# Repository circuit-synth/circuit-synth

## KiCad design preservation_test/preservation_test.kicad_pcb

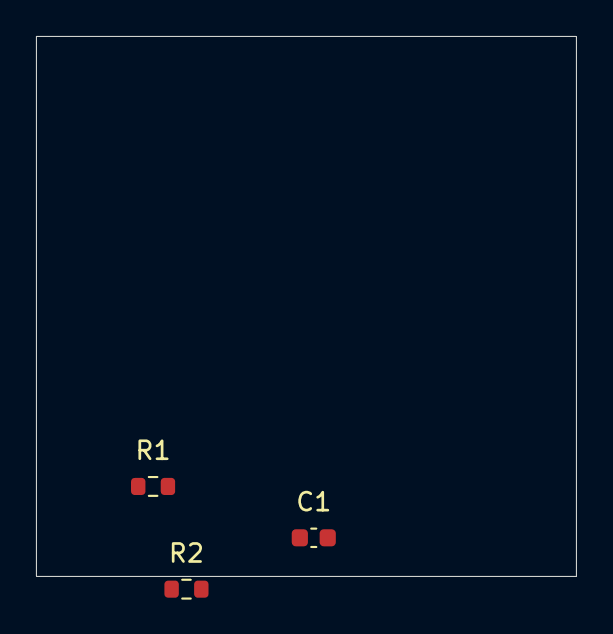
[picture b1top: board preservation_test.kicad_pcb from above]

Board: 2 copper layers, 30.0 x 30.0 mm, 3 parts (0 on the bottom side), 2 nets, no tracks yet.

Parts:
C1: 100nF; C_0603_1608Metric
R1: 10k; R_0603_1608Metric
R2: 1k; R_0603_1608Metric

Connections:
GND: C1.2, R2.2
SIGNAL: C1.1, R1.2, R2.1

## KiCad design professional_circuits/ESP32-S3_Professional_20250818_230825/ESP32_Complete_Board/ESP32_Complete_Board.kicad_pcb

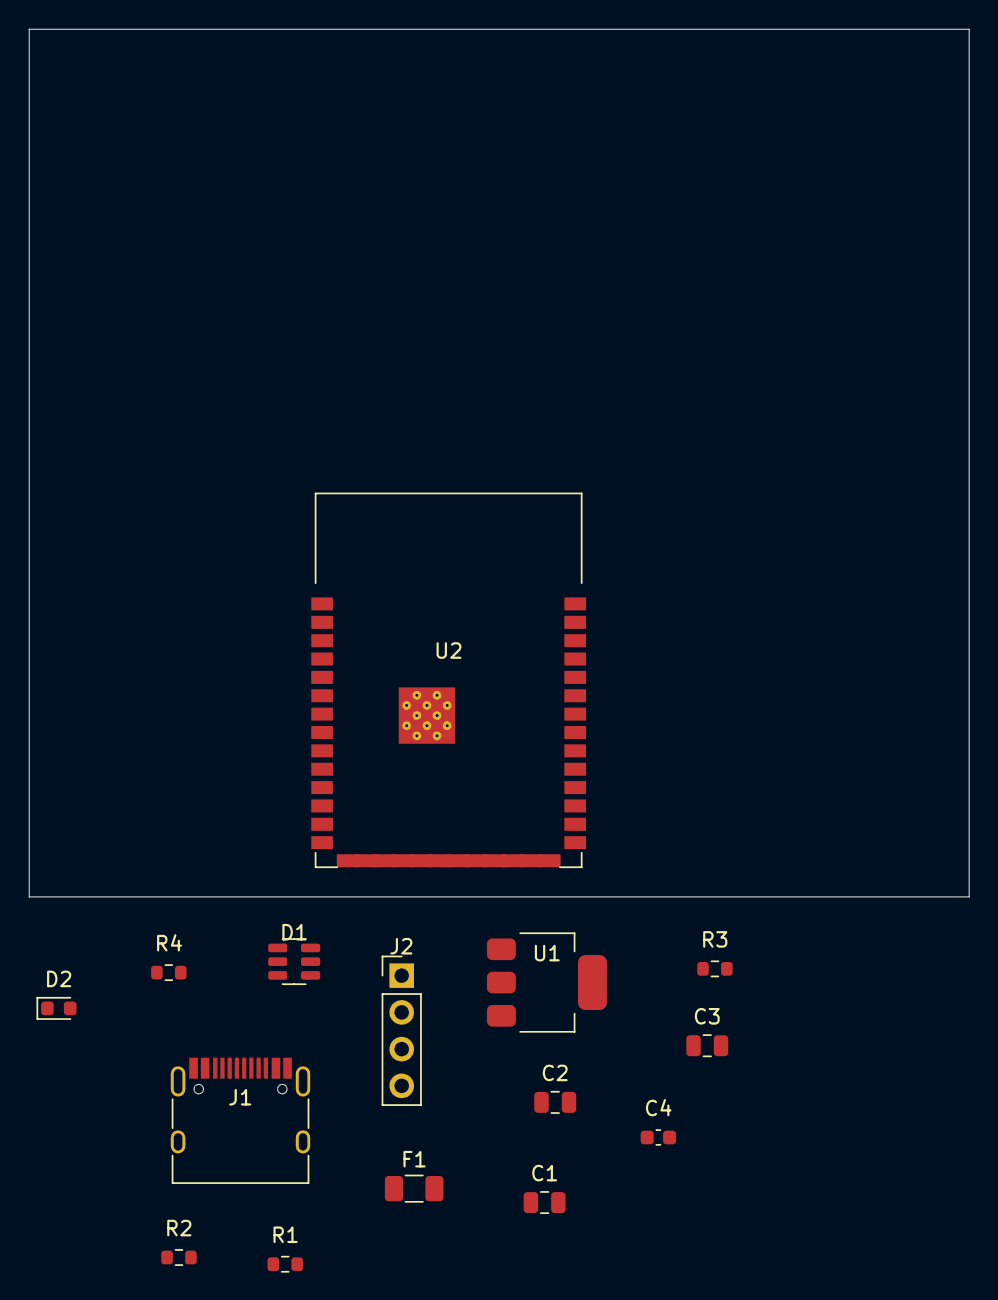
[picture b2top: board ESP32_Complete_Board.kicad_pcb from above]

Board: 2 copper layers, 65.0 x 60.0 mm, 15 parts (0 on the bottom side), 15 nets, no tracks yet.

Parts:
C1, C3: 10uF; C_0805_2012Metric
C2: 22uF; C_0805_2012Metric
C4: 100nF; C_0603_1608Metric
D1: SOT-23-6
D2: LED_0603_1608Metric
F1: 2A; Fuse_1206_3216Metric
J1: USB_C_Receptacle_HRO_TYPE-C-31-M-12
J2: PinHeader_1x04_P2.54mm_Vertical
R1, R2: 5.1k; R_0603_1608Metric
R3: 10k; R_0603_1608Metric
R4: 220; R_0603_1608Metric
U1: SOT-223-3_TabPin2
U2: ESP32-S3-WROOM-1

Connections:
DEBUG_RX: J2.4, U2.36
DEBUG_TX: J2.3, U2.37
GND: C1.2, C2.2, C3.2, C4.2, D1.2, D2.1, J1.A1, J1.A12, J1.B1, J1.B12, J2.2, R1.2, R2.2, U1.1, U2.1, U2.40, U2.41
LED_CONTROL: R4.1, U2.12
unnamed: F1.1, J1.A4, J1.A9, J1.B4, J1.B9
unnamed: D1.1, J1.A6, J1.B6
unnamed: D1.3, J1.A7, J1.B7
unnamed: J1.A5, R1.1
unnamed: J1.B5, R2.1
unnamed: R3.2, U2.3
unnamed: D2.2, R4.2
USB_DM: D1.4, U2.13
USB_DP: D1.6, U2.14
VBUS: C1.1, D1.5, F1.2, U1.3
VCC_3V3: C2.1, C3.1, C4.1, J2.1, R3.1, U1.2, U2.2

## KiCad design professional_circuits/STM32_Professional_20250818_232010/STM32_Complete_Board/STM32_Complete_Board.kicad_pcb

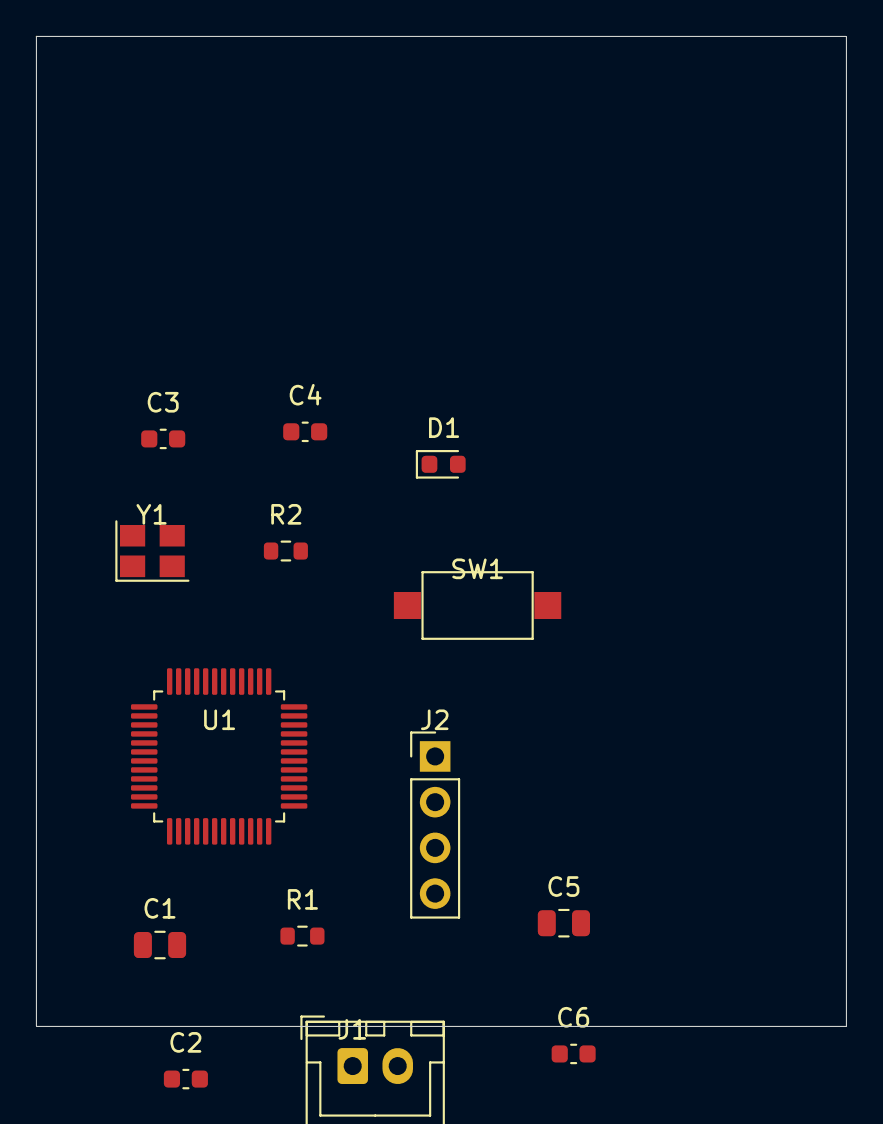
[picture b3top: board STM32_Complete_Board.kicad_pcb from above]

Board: 2 copper layers, 45.0 x 55.0 mm, 14 parts (0 on the bottom side), 9 nets, no tracks yet.

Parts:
C1, C5: 10uF; C_0805_2012Metric
C2, C6: 100nF; C_0603_1608Metric
C3, C4: 18pF; C_0603_1608Metric
D1: LED_0603_1608Metric
J1: JST_XH_B2B-XH-A_1x02_P2.50mm_Vertical
J2: PinHeader_1x04_P2.54mm_Vertical
R1: 10k; R_0603_1608Metric
R2: 220; R_0603_1608Metric
SW1: SW_SPST_CK_RS282G05A3
U1: LQFP-48_7x7mm_P0.5mm
Y1: 8MHz; Crystal_SMD_3225-4Pin_3.2x2.5mm

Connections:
GND: C1.2, C2.2, C3.2, C4.2, C5.2, C6.2, D1.1, J1.2, J2.2, SW1.2, U1.8, U1.23, U1.35, U1.47
LED_CONTROL: R2.1, U1.15
unnamed: C3.1, U1.5, Y1.1
unnamed: C4.1, U1.6, Y1.2
unnamed: D1.2, R2.2
SWCLK: J2.4, U1.37
SWDIO: J2.3, U1.34
VCC_3V3: C1.1, C2.1, C5.1, C6.1, J1.1, J2.1, R1.1, U1.9, U1.24, U1.36, U1.48
nRESET: R1.2, SW1.1, U1.7

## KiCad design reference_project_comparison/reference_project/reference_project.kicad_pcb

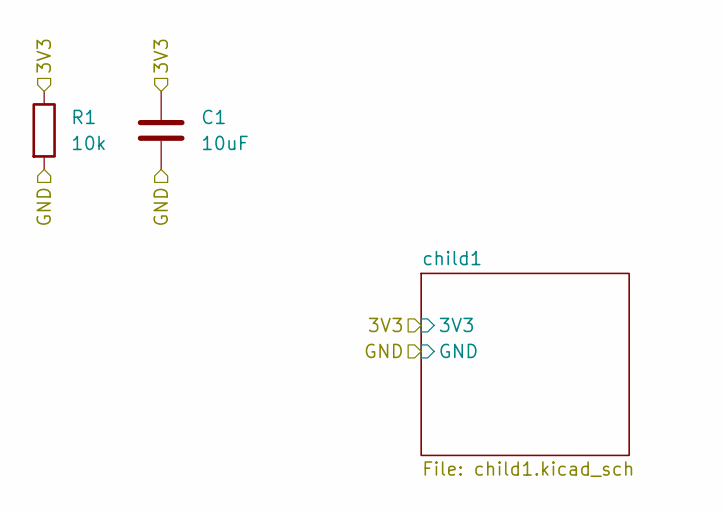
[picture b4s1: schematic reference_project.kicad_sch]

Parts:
C1: 10uF; C_0603_1608Metric
R1: 10k; R_0603_1608Metric

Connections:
/3V3: C1.1, R1.1; also elsewhere on the board
/GND: C1.2, R1.2; also elsewhere on the board

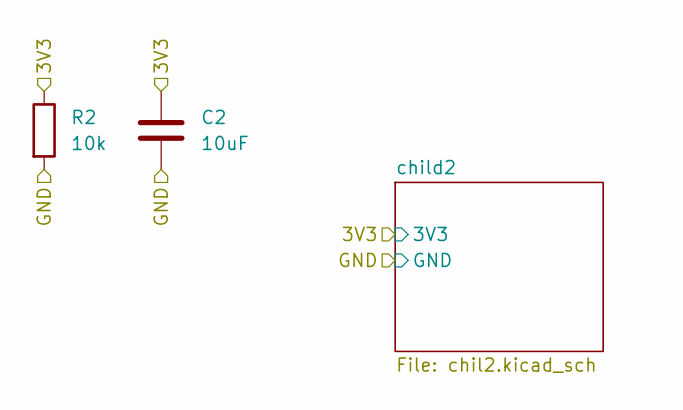
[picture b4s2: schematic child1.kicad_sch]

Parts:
C2: 10uF; C_0603_1608Metric
R2: 10k; R_0603_1608Metric

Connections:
/3V3: C2.1, R2.1; also elsewhere on the board
/GND: C2.2, R2.2; also elsewhere on the board

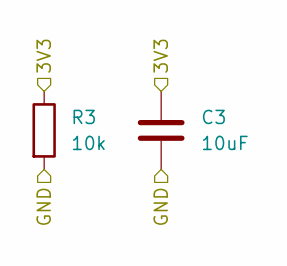
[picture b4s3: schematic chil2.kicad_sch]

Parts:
C3: 10uF; C_0603_1608Metric
R3: 10k; R_0603_1608Metric

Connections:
/3V3: C3.1, R3.1; also elsewhere on the board
/GND: C3.2, R3.2; also elsewhere on the board

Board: 2 copper layers, 6 parts (0 on the bottom side), 2 nets, no tracks yet.
